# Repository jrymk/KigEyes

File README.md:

# Project KigEyes

Video passthrough and electronic eye for Kigurumi masks

## Project structure

| Directory | Description | Source status |
| --- | --- | --- |
| [companion](companion/) | Android app for connection setup, screen sharing, wearer viewing and phone-camera capture | Published |
| [docs](docs/) | Project documentation and illustrations | Selected files published |
| [drivers](drivers/) | Linux hardware drivers and device services | Partially published |
| `drivers/bluetooth` | Bluetooth compatibility fixes for controller input and haptics | Not published |
| `drivers/ec` | Linux link to the embedded controller: telemetry, commands and shutdown coordination | Not published |
| `drivers/glasses` | AR-glasses display control, IMU readings and orientation processing | Not published |
| [drivers/imx675](drivers/imx675/) | Linux sensor driver and device-tree support for KigEyes IMX675 modules | Core driver published |
| `drivers/imx675/libcamera` | IMX675 camera-stack integration and image-processing tuning | Not published |
| `drivers/imx678` | Experimental driver and bring-up tools for the IMX678 camera module | Not published |
| `firmware` | Microcontroller firmware for the custom boards | Not published |
| `firmware/camera-module` | Camera-module power sequencing, sensor management and synchronization controls | Publishing soon |
| `firmware/mainboard` | Mainboard controller, host communication and board diagnostics | Not published |
| `firmware/power-io-board` | Battery charging, power delivery, protection and power-state control | Not published |
| [integrations](integrations/) | Optional phone-mirroring and media integrations | Phone worker published |
| `integrations/jellyfin` | Jellyfin casting, playback and remote controls | Private |
| [integrations/scrcpy](integrations/scrcpy/) | Pi-side phone receiver, installation tools and Visor integration | Private |
| [integrations/scrcpy/worker](integrations/scrcpy/worker/) | Modified Android scrcpy worker with direct TLS, reconnection and panel controls | Published |
| `integrations/spotify` | Spotify Connect receiver integration and playback controls | Private |
| [licenses](licenses/) | License texts for published software and hardware | Published |
| [PCB](PCB/) | Schematics, PCB layouts and manufacturing files | Selected designs published |
| `PCB/eye-tracker-mainboard` | Eye-tracking controller board development | Publishing soon |
| `PCB/IMX675-camera-module` | Custom IMX675 sensor module and its management circuitry | Publishing soon |
| `PCB/IMX678-renheng-adaptor` | Adapter and management board for the Renheng IMX678 module | Publishing soon |
| `PCB/kigeyes-mainboard` | Compute Module 5 carrier with camera, display and peripheral connections | v1 work in progress |
| [PCB/kigeyes-power-io-board](PCB/kigeyes-power-io-board/) | Battery, charging, power conversion and peripheral power board | v2 work in progress |
| [PCB/OVM6211-bga2lga](PCB/OVM6211-bga2lga/) | OVM6211 sensor package adapter board | Published |
| [PCB/OVM6211-fpc](PCB/OVM6211-fpc/) | Flexible OVM6211 camera board for eye-tracking hardware | Published |
| `STL` | Printable mask parts, mounts and mechanical prototypes | Not published yet |
| `visor` | On-mask passthrough, display composition, HUD and system control | Private |

## Open source status

This project is not fully open source for now.

- **All** general-purpose designs and reusable components that may benefit the open-source community will be released in full, such as camera sensor drivers, breakout boards, and eye tracking algorithms.
- **Most** schematics will be released in full
- **Some** PCB design files and Gerbers remain closed until obsolete
- **Most** firmware and source code will be released in full
- **Some** mechanical design files will be released in full

## KiCad library

KiCad library available at [jrymk/jerrymk_kicad_lib](https://github.com/jrymk/jerrymk_kicad_lib).

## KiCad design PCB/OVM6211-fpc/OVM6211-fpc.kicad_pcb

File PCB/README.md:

# Project KigEyes PCBs

## kigeyes-mainboard

| versions | status |
| :-- | :-- |
| prototype | assembled, waiting for HDMI to DP converter, do not build |
| v1 | pending |

- Type C (custom protocol) power input (up to 15V) from `kigeyes-power-io-board`, includes single USB 2.0, dual USB 3.2 Gen 1, and I2C
- Raspberry Pi Compute Module 5
- HDMI to DisplayPort to Type C DP Alt mode converter
- MIPI camera multiplexer to connect up to 4 cameras (2 active at once)

## kigeyes-power-io-board

|  |  |
| --- | --- |

| versions | status |
| :-- | :-- |
| [v1](https://github.com/jrymk/KigEyes/tree/dbb5fbab16420fb983b5ba6c4678849511922e23/PCB/kigeyes-power-io-board) | finalized, tested |

- USB PD input (up to 15V 3A)
- 1S LiFePO4 BQ25306 charger (up to 3A) and voltage booster
- Type C (custom protocol) power output (5~15V) to `kigeyes-mainboard`
- USB 2.0 hub
- USB Type C DFP (5V 1.5A, USB 3.2 Gen 1, PD-compliant)
- USB Type A DFP (5V 0.9A guaranteed, USB 3.2 Gen 1)
- USB Port AUX (JST PH, USB 2.0)
- USB Port ENV (JST PH, USB 2.0)
- 24V/12V fan output with speed control

## IMX675-camera-module

- IMX675 sensor with
    - reasonable sensor size (1/2.8") for conical M12 lenses for a small opening
    - reasonably high resolution (2592×1944 5.12MP) for clear text reading but not too high to be wasteful by the mediocre resolution of conical lenses, Raspberry Pi processing power, and 1080p AR glasses
    - STARVIS 2 for okay low light performance
- MCU controlled power sequencing, power rail monitoring, and sensor configuration
- LED status indication
- Stereo camera sync signals through the 22P connector

Note: Use opposite-side (B-type) 22P 0.5mm FFC cables

| versions | status |
| :-- | :-- |
| v1 | tested |

## eye-tracker-mainboard

| versions | status |
| :-- | :-- |
| [a1](https://github.com/jrymk/KigEyes/tree/e749d2dd36b2bbe4de054390257230e3775aa7c6/PCB/archive/eye-tracker-mainboard) | scrapped |
| v1 | postponed |

- Dual ESP32P4 processors
- Connectors to `OVM6211-fpc`
- USB 2.0 hub

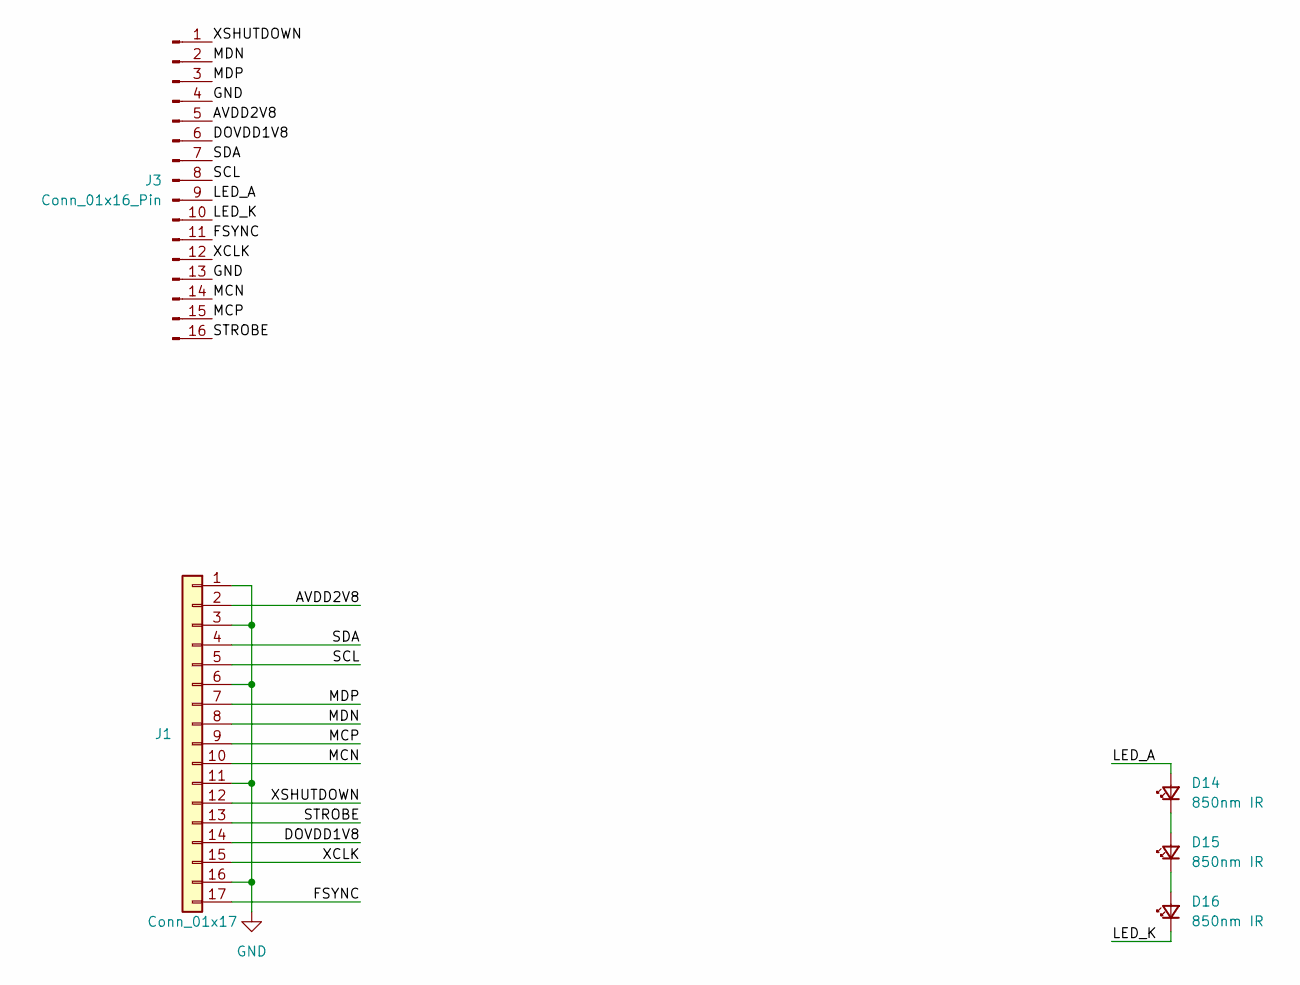
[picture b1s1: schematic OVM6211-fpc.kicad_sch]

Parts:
D14, D15, D16: 850nm IR; LED_0603_1608Metric
J1: Conn_01x17; OVM6211-lga-fp
J3: Conn_01x16_Pin; FFC_16P_BoardEdge

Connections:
/AVDD2V8: J1.2, J3.5
/DOVDD1V8: J1.14, J3.6
/FSYNC: J1.17, J3.11
/LED_A: D14.2 (A), J3.9
/LED_K: D16.1 (K), J3.10
/MCN: J1.10, J3.14
/MCP: J1.9, J3.15
/MDN: J1.8, J3.2
/MDP: J1.7, J3.3
/SCL: J1.5, J3.8
/SDA: J1.4, J3.7
/STROBE: J1.13, J3.16
/XCLK: J1.15, J3.12
/XSHUTDOWN: J1.12, J3.1
GND: J1.1, J1.3, J1.6, J1.11, J1.16, J3.4, J3.13
unnamed: D14.1 (K), D15.2 (A)
unnamed: D15.1 (K), D16.2 (A)

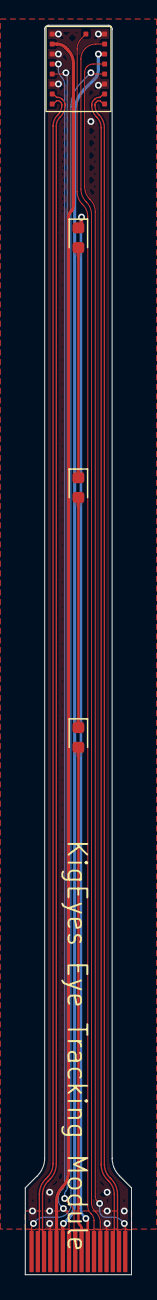
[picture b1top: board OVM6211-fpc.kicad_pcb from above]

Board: 2 copper layers, 8.5 x 100.0 mm, 5 parts (0 on the bottom side), 17 nets.

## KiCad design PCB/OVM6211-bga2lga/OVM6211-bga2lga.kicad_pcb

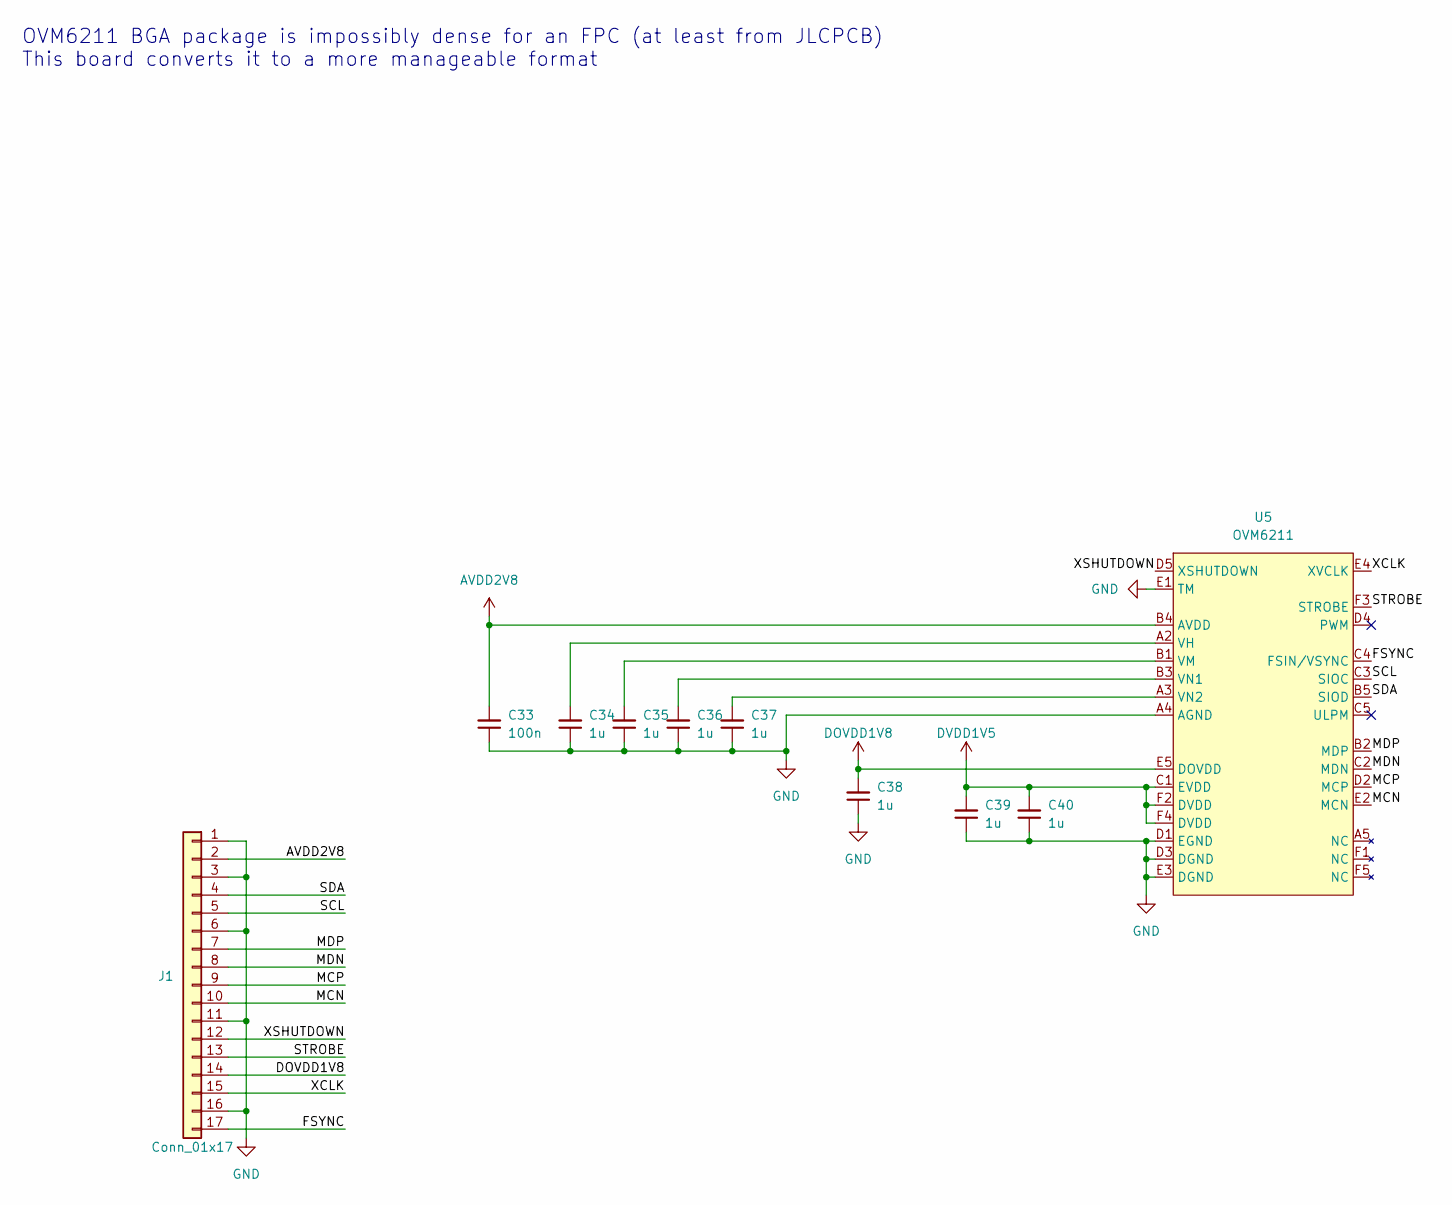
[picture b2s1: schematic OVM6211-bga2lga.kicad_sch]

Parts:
C33: 100n; C_0201_0603Metric
C34, C35, C36, C37, C38, C39, C40: 1u; C_0201_0603Metric
J1: Conn_01x17; OVM6211-lga
U5: OVM6211

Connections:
/FSYNC: J1.17, U5.C4 (FSIN/VSYNC)
/MCN: J1.10, U5.E2 (MCN)
/MCP: J1.9, U5.D2 (MCP)
/MDN: J1.8, U5.C2 (MDN)
/MDP: J1.7, U5.B2 (MDP)
/SCL: J1.5, U5.C3 (SIOC)
/SDA: J1.4, U5.B5 (SIOD)
/STROBE: J1.13, U5.F3 (STROBE)
/XCLK: J1.15, U5.E4 (XVCLK)
/XSHUTDOWN: J1.12, U5.D5 (XSHUTDOWN)
AVDD2V8: C33.2, J1.2, U5.B4 (AVDD)
DOVDD1V8: C38.2, J1.14, U5.E5 (DOVDD)
DVDD1V5: C39.2, C40.2, U5.C1 (EVDD), U5.F2 (DVDD), U5.F4 (DVDD)
GND: C33.1, C34.1, C35.1, C36.1, C37.1, C38.1, C39.1, C40.1, J1.1, J1.3, J1.6, J1.11, J1.16, U5.A4 (AGND), U5.D1 (EGND), U5.D3 (DGND), U5.E1 (TM), U5.E3 (DGND)
unnamed: C34.2, U5.A2 (VH)
unnamed: C35.2, U5.B1 (VM)
unnamed: C36.2, U5.B3 (VN1)
unnamed: C37.2, U5.A3 (VN2)

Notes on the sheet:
OVM6211 BGA package is impossibly dense for an FPC (at least from JLCPCB) This board converts it to a more manageable format

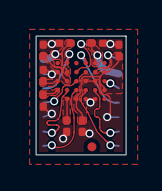
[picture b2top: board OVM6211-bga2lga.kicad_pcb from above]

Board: 4 copper layers, 5.0 x 6.6 mm, 10 parts (0 on the bottom side), 18 nets.

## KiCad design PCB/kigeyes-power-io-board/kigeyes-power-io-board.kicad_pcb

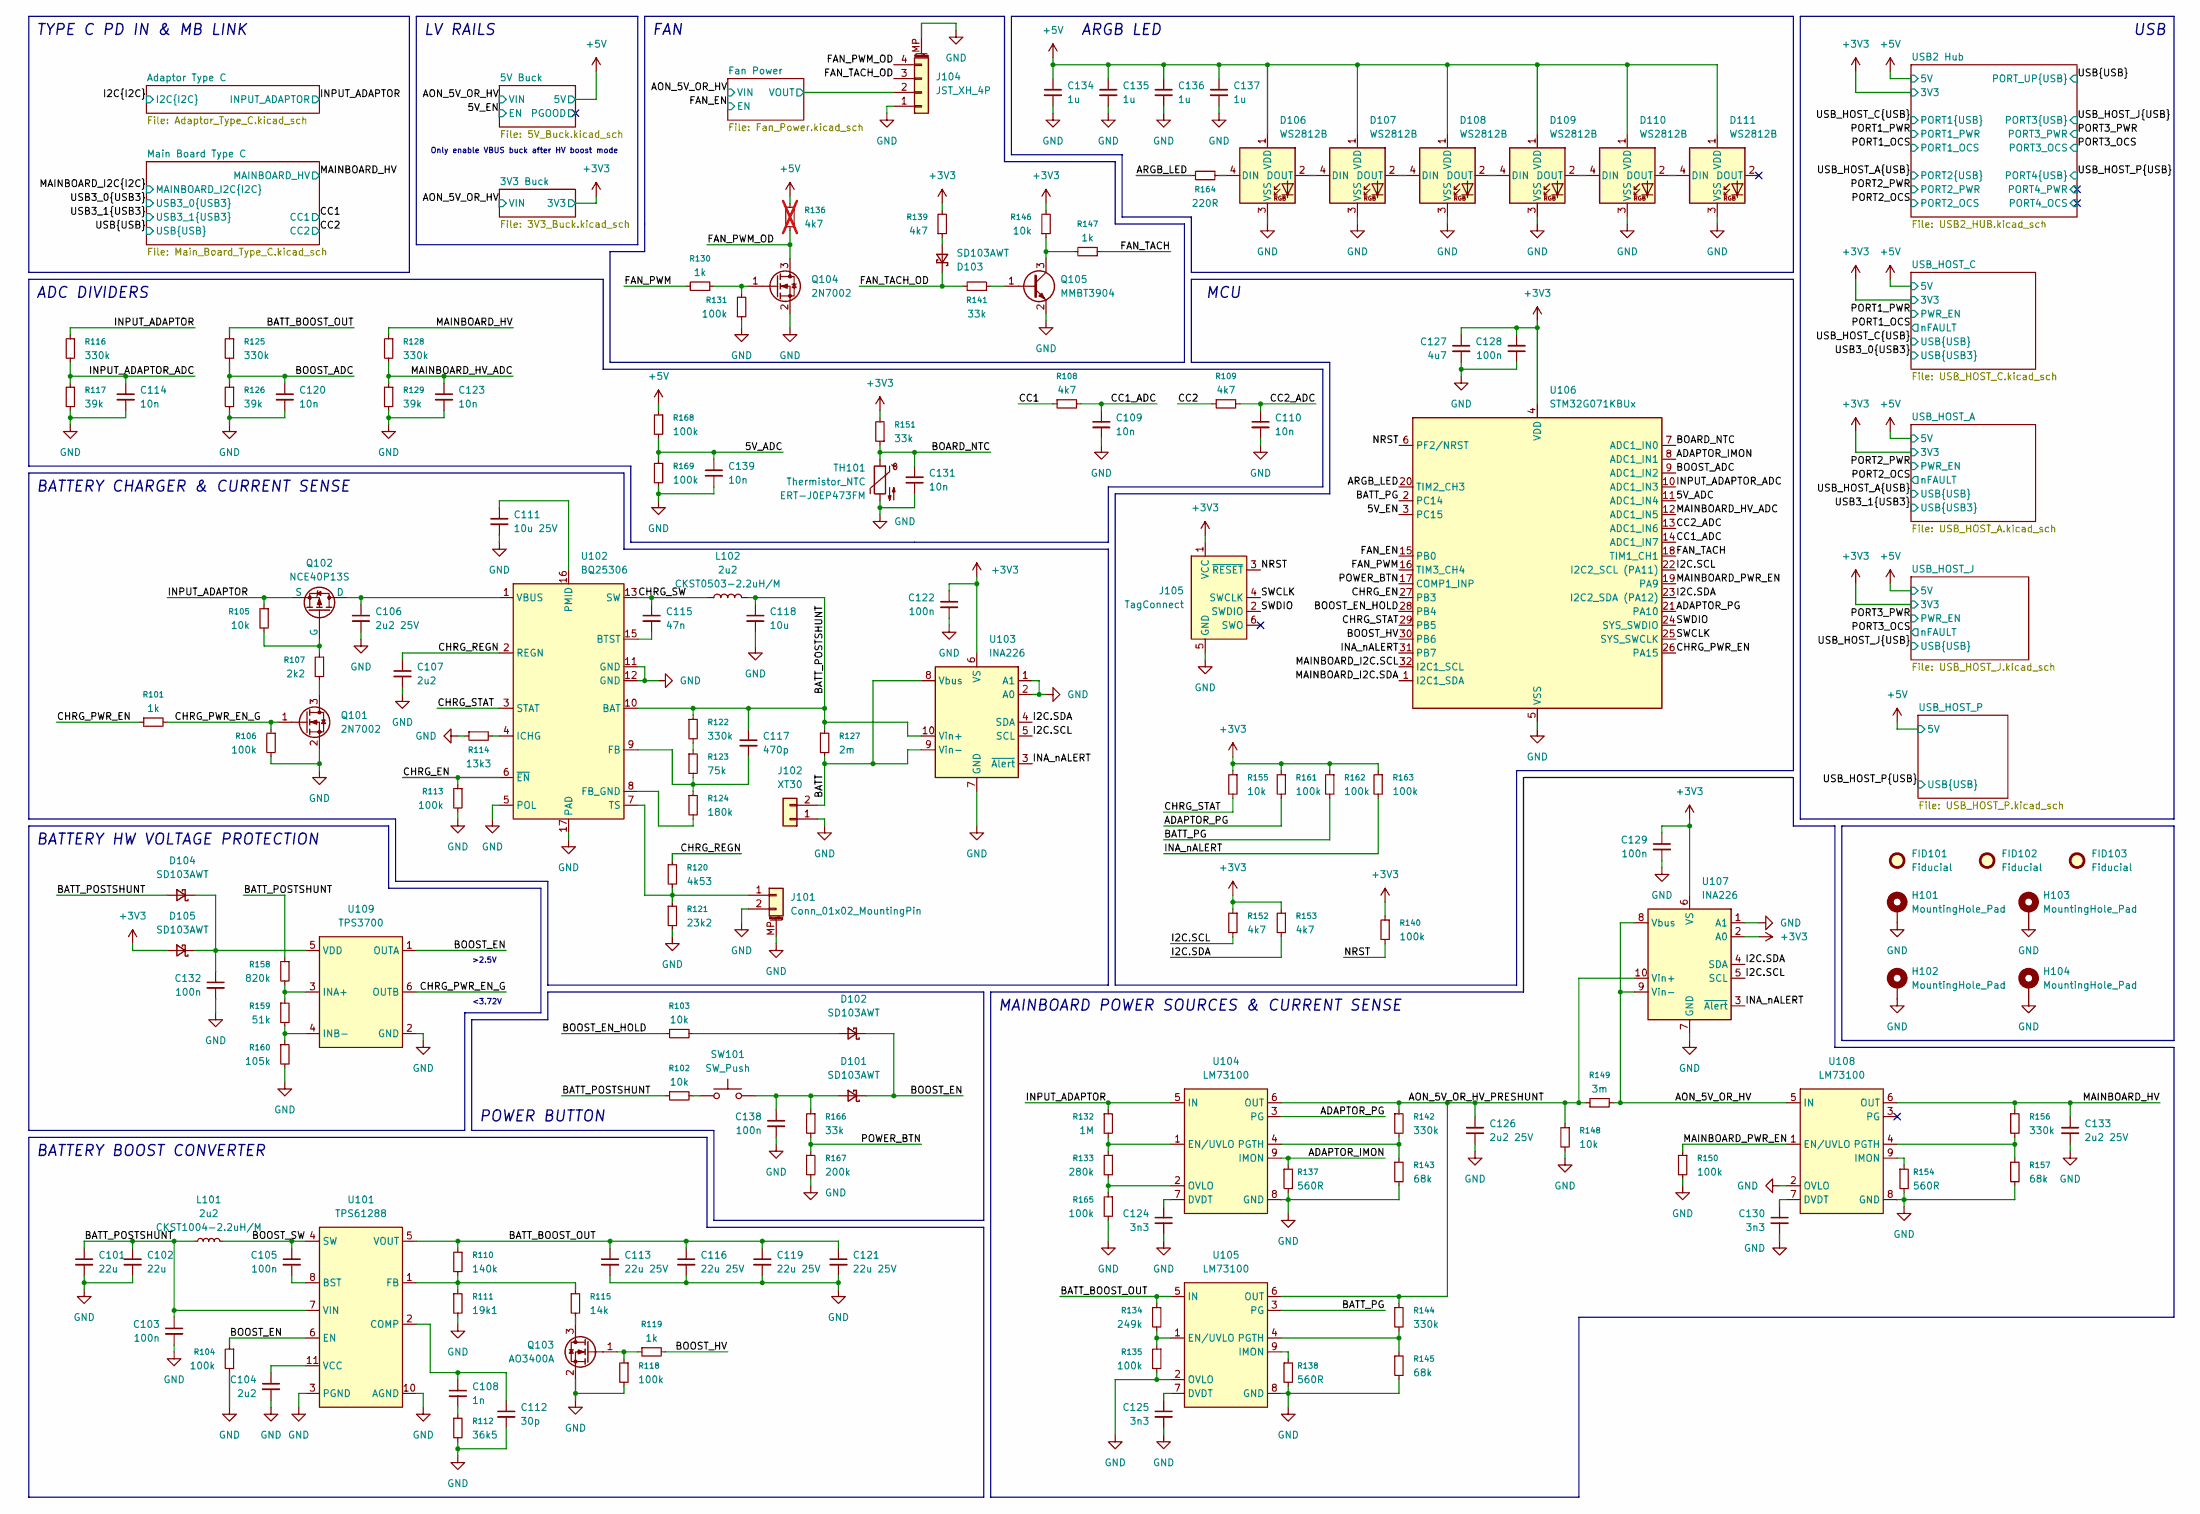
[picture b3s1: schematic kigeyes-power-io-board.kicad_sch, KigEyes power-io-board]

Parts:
C101, C102: 22u; C_0603_1608Metric
C103, C105, C122, C128, C129, C132, C138: 100n; C_0402_1005Metric
C104, C107: 2u2; C_0402_1005Metric
C106, C126, C133: 2u2 25V; C_0603_1608Metric
C108: 1n; C_0402_1005Metric
C109, C110, C114, C120, C123, C131, C139: 10n; C_0402_1005Metric
C111: 10u 25V; C_0805_2012Metric
C112: 30p; C_0402_1005Metric
C113, C116, C119, C121: 22u 25V; C_0805_2012Metric
C115: 47n; C_0402_1005Metric
C117: 470p; C_0402_1005Metric
C118: 10u; C_0603_1608Metric
C124, C125, C130: 3n3; C_0402_1005Metric
C127: 4u7; C_0603_1608Metric
C134, C135, C136, C137: 1u; C_0402_1005Metric
D101, D102, D103, D104, D105: SD103AWT; D_SOD-523
D106, D107, D108, D109, D110, D111: WS2812B; WS2812B-1515
FID101, FID102, FID103: Fiducial; Fiducial_0.5mm_Mask1mm
H101, H102, H103, H104: MountingHole_Pad; MountingHole_2.7mm_M2.5_ISO14580_Pad_TopBottom
J101: Conn_01x02_MountingPin; JST_PH_S2B-PH-SM4-TB_1x02-1MP_P2.00mm_Horizontal
J102: XT30; AMASS_XT30PW-M_1x02_P2.50mm_Horizontal
J104: JST_XH_4P; JST_XH_S4B-XH-SM4-TB_1x04-1MP_P2.50mm_Horizontal
J105: TagConnect; Tag-Connect_TC2030-IDC-NL_2x03_P1.27mm_Vertical
L101: 2u2; L_CKST1004; Part No. CKST1004-2.2uH/M
L102: 2u2; L_CKST0503; Part No. CKST0503-2.2uH/M
Q101, Q104: 2N7002; SOT-23
Q102: NCE40P13S; SOP-8_3.76x4.96mm_P1.27mm_NCE40P13S
Q103: AO3400A; SOT-23
Q105: MMBT3904; SOT-23
R101, R119, R130, R147: 1k; R_0402_1005Metric
R102, R103, R105, R146, R155: 10k; R_0402_1005Metric
R104, R106, R113, R118, R131, R135, R140, R150, R161, R162, R163, R165, R168, R169: 100k; R_0402_1005Metric
R107: 2k2; R_0402_1005Metric
R108, R109, R139, R152, R153: 4k7; R_0402_1005Metric
R110: 140k; R_0402_1005Metric
R111: 19k1; R_0402_1005Metric
R112: 36k5; R_0402_1005Metric
R114: 13k3; R_0402_1005Metric
R115: 14k; R_0402_1005Metric
R116, R122, R125, R128, R142, R144, R156: 330k; R_0402_1005Metric
R117, R126, R129: 39k; R_0402_1005Metric
R120: 4k53; R_0402_1005Metric
R121: 23k2; R_0402_1005Metric
R123: 75k; R_0402_1005Metric
R124: 180k; R_0402_1005Metric
R127: 2m; R_2512_6332Metric
R132: 1M; R_0402_1005Metric
R133: 280k; R_0402_1005Metric
R134: 249k; R_0402_1005Metric
R136: 4k7; R_0402_1005Metric; not fitted
R137, R138, R154: 560R; R_0402_1005Metric
R141, R151, R166: 33k; R_0402_1005Metric
R143, R145, R157: 68k; R_0402_1005Metric
R148: 10k; R_0805_2012Metric
R149: 3m; R_1206_3216Metric
R158: 820k; R_0402_1005Metric
R159: 51k; R_0402_1005Metric
R160: 105k; R_0402_1005Metric
R164: 220R; R_0402_1005Metric
R167: 200k; R_0402_1005Metric
SW101: SW_Push; SW_Tactile_SPST_Angled_PTS645Vx58-2LFS
TH101: Thermistor_NTC; R_0402_1005Metric; Part number ERT-J0EP473FM
U101: TPS61288; Texas_VQFN-HR-20_3x2.5mm_P0.5mm_RQQ0011A
U102: BQ25306; WQFN-16-1EP_3x3mm_P0.5mm_EP1.68x1.68mm
U103, U107: INA226; TSSOP-10_3x3mm_P0.5mm
U104, U105, U108: LM73100; Texas VQFN-HR 2x2mm RPW0010A
U106: STM32G071KBUx; QFN-32-1EP_5x5mm_P0.5mm_EP3.45x3.45mm
U109: TPS3700; SOT-23-6

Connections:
+3V3: C122.1, C127.1, C128.2, C129.1, D105.2 (A), J105.1 (VCC), R139.2, R140.1, R146.2, R151.2, R152.1, R153.1, R155.1, R161.1, R162.1, R163.1, U103.6 (VS), U106.4 (VDD), U107.2 (A0), U107.6 (VS); also elsewhere on the board
+5V: C134.1, C135.1, C136.1, C137.1, D106.1 (VDD), D107.1 (VDD), D108.1 (VDD), D109.1 (VDD), D110.1 (VDD), D111.1 (VDD), R136.1, R168.1; also elsewhere on the board
/5V_ADC: C139.1, R168.2, R169.1, U106.11 (ADC1_IN4)
/5V_EN: U106.3 (PC15); also elsewhere on the board
/ADAPTOR_IMON: R137.1, U104.9 (IMON), U106.8 (ADC1_IN1)
/ADAPTOR_PG: R161.2, U104.3 (PG), U106.21 (PA10)
/AON_5V_OR_HV: R149.2, U107.8 (Vbus), U107.9 (Vin-), U108.5 (IN); also elsewhere on the board
/AON_5V_OR_HV_PRESHUNT: C126.1, R142.1, R144.1, R148.1, R149.1, U104.6 (OUT), U105.6 (OUT), U107.10 (Vin+)
/ARGB_LED: R164.2, U106.20 (TIM2_CH3)
/BATT: J102.2, R127.2, U103.8 (Vbus), U103.9 (Vin-)
/BATT_BOOST_OUT: C113.1, C116.1, C119.1, C121.1, R110.1, R125.1, R134.1, U101.5 (VOUT), U105.5 (IN)
/BATT_PG: R162.2, U105.3 (PG), U106.2 (PC14)
/BATT_POSTSHUNT: C101.1, C102.1, C103.1, C117.1, C118.1, D104.2 (A), L101.1, L102.2, R102.1, R122.1, R127.1, R158.1, U101.7 (VIN), U102.10 (BAT), U103.10 (Vin+)
/BOARD_NTC: C131.2, R151.1, TH101.1, U106.7 (ADC1_IN0)
/BOOST_ADC: C120.1, R125.2, R126.1, U106.9 (ADC1_IN2)
/BOOST_EN: D101.1 (K), D102.1 (K), R104.1, U101.6 (EN), U109.1 (OUTA)
/BOOST_EN_HOLD: R103.1, U106.28 (PB4)
/BOOST_HV: R119.2, U106.30 (PB6)
/BOOST_SW: C105.1, L101.2, U101.4 (SW), U101.9 (SW)
/CC1: R108.1; also elsewhere on the board
/CC1_ADC: C109.1, R108.2, U106.14 (ADC1_IN7)
/CC2: R109.1; also elsewhere on the board
/CC2_ADC: C110.1, R109.2, U106.13 (ADC1_IN6)
/CHRG_EN: R113.1, U102.6 (~EN), U106.27 (PB3)
/CHRG_PWR_EN: R101.1, U106.26 (PA15)
/CHRG_PWR_EN_G: Q101.1 (G), R101.2, R106.1, U109.6 (OUTB)
/CHRG_REGN: C107.1, R120.1, U102.2 (REGN)
/CHRG_STAT: R155.2, U102.3 (STAT), U106.29 (PB5)
/CHRG_SW: C115.1, L102.1, U102.13 (SW), U102.14 (SW)
/FAN_EN: U106.15 (PB0); also elsewhere on the board
/FAN_PWM: R130.2, U106.16 (TIM3_CH4)
/FAN_PWM_OD: J104.4, Q104.3 (D), R136.2
/FAN_TACH: R147.1, U106.18 (TIM1_CH1)
/FAN_TACH_OD: D103.1 (K), J104.3, R141.2
/Fan Power/VOUT: J104.2; also elsewhere on the board
/I2C.SCL: R152.2, U103.5 (SCL), U106.22 (I2C2_SCL (PA11)), U107.5 (SCL); also elsewhere on the board
/I2C.SDA: R153.2, U103.4 (SDA), U106.23 (I2C2_SDA (PA12)), U107.4 (SDA); also elsewhere on the board
/INA_nALERT: R163.2, U103.3 (~Alert), U106.31 (PB7), U107.3 (~Alert)
/INPUT_ADAPTOR: Q102.3 (S), R105.1, R116.1, R132.1, U104.5 (IN); also elsewhere on the board
/INPUT_ADAPTOR_ADC: C114.1, R116.2, R117.1, U106.10 (ADC1_IN3)
/MAINBOARD_HV: C133.1, R128.1, R156.1, U108.6 (OUT); also elsewhere on the board
/MAINBOARD_HV_ADC: C123.1, R128.2, R129.1, U106.12 (ADC1_IN5)
/MAINBOARD_I2C.SCL: U106.32 (I2C1_SCL); also elsewhere on the board
/MAINBOARD_I2C.SDA: U106.1 (I2C1_SDA); also elsewhere on the board
/MAINBOARD_PWR_EN: R150.1, U106.19 (PA9), U108.1 (EN/UVLO)
/NRST: J105.3 (~RESET), R140.2, U106.6 (PF2/NRST)
/POWER_BTN: R166.2, R167.1, U106.17 (COMP1_INP)
/SWCLK: J105.4 (SWCLK), U106.25 (SYS_SWCLK)
/SWDIO: J105.2 (SWDIO), U106.24 (SYS_SWDIO)
GND: C101.2, C102.2, C103.2, C104.2, C106.2, C107.2, C109.2, C110.2, C111.2, C112.2, C113.2, C114.2, C116.2, C118.2, C119.2, C120.2, C121.2, C122.2, C123.2, C124.2, C125.2, C126.2, C127.2, C128.1, C129.2, C130.2, C131.1, C132.2, C133.2, C134.2, C135.2, C136.2, C137.2, C138.2, C139.2, D106.3 (VSS), D107.3 (VSS), D108.3 (VSS), D109.3 (VSS), D110.3 (VSS), D111.3 (VSS), H101.1 (1_1), H102.1 (1_1), H103.1 (1_1), H104.1 (1_1), J101.2, J101.MP (MountPin), J102.1, J104.1, J104.MP (MountPin), J105.5 (GND), Q101.2 (S), Q103.2 (S), Q104.2 (S), Q105.2 (E), R104.2, R106.2, R111.2, R112.2, R113.2, R114.1, R117.2, R118.2, R121.2, R126.2, R129.2, R131.1, R135.2, R137.2, R138.2, R143.2, R145.2, R148.2, R150.2, R154.2, R157.2, R160.2, R165.2, R167.2, R169.2, TH101.2, U101.3 (PGND), U101.10 (AGND), U102.5 (POL), U102.11 (GND), U102.12 (GND), U102.17 (PAD), U103.1 (A1), U103.2 (A0), U103.7 (GND), U104.8 (GND), U105.2 (OVLO), U105.8 (GND), U106.5 (VSS), U106.33 (VSS), U107.1 (A1), U107.7 (GND), U108.2 (OVLO), U108.8 (GND), U109.2 (GND); also elsewhere on the board
unnamed: C108.2, R112.1
unnamed: C138.1, D101.2 (A), R166.1, SW101.1
unnamed: D102.2 (A), R103.2
unnamed: D103.2 (A), R139.1
unnamed: C132.1, D104.1 (K), D105.1 (K), U109.5 (VDD)
unnamed: D106.4 (DIN), R164.1
unnamed: D106.2 (DOUT), D107.4 (DIN)
unnamed: D107.2 (DOUT), D108.4 (DIN)
unnamed: D108.2 (DOUT), D109.4 (DIN)
unnamed: D109.2 (DOUT), D110.4 (DIN)
unnamed: D110.2 (DOUT), D111.4 (DIN)
unnamed: J101.1, R120.2, R121.1, U102.7 (TS)
unnamed: Q101.3 (D), R107.2
unnamed: C106.1, Q102.1 (D), U102.1 (VBUS)
unnamed: Q102.2 (G), R105.2, R107.1
unnamed: Q103.3 (D), R115.2
unnamed: Q103.1 (G), R118.1, R119.1
unnamed: Q104.1 (G), R130.1, R131.2
unnamed: Q105.1 (B), R141.1
unnamed: Q105.3 (C), R146.1, R147.2
unnamed: R102.2, SW101.2
unnamed: R122.2, R123.1
unnamed: C105.2, U101.8 (BST)
unnamed: C108.1, C112.1, U101.2 (COMP)
unnamed: R110.2, R111.1, R115.1, U101.1 (FB)
unnamed: C104.1, U101.11 (VCC)
unnamed: C115.2, U102.15 (BTST)
unnamed: C117.2, R123.2, R124.1, U102.9 (FB)
unnamed: R124.2, U102.8 (FB_GND)
unnamed: R114.2, U102.4 (ICHG)
unnamed: C111.1, U102.16 (PMID)
unnamed: C124.1, U104.7 (DVDT)
unnamed: R132.2, R133.1, U104.1 (EN/UVLO)
unnamed: R133.2, R165.1, U104.2 (OVLO)
unnamed: R142.2, R143.1, U104.4 (PGTH)
unnamed: C125.1, U105.7 (DVDT)
unnamed: R134.2, R135.1, U105.1 (EN/UVLO)
unnamed: R138.1, U105.9 (IMON)
unnamed: R144.2, R145.1, U105.4 (PGTH)
unnamed: C130.1, U108.7 (DVDT)
unnamed: R154.1, U108.9 (IMON)
unnamed: R156.2, R157.1, U108.4 (PGTH)
unnamed: R158.2, R159.1, U109.3 (INA+)
unnamed: R159.2, R160.1, U109.4 (INB-)

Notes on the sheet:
Only enable VBUS buck after HV boost mode
ADC DIVIDERS
<3.72V
BATTERY BOOST CONVERTER
FAN
USB
TYPE C PD IN & MB LINK
ARGB LED
>2.5V
POWER BUTTON
MCU
MAINBOARD POWER SOURCES & CURRENT SENSE
BATTERY HW VOLTAGE PROTECTION
BATTERY CHARGER & CURRENT SENSE
LV RAILS

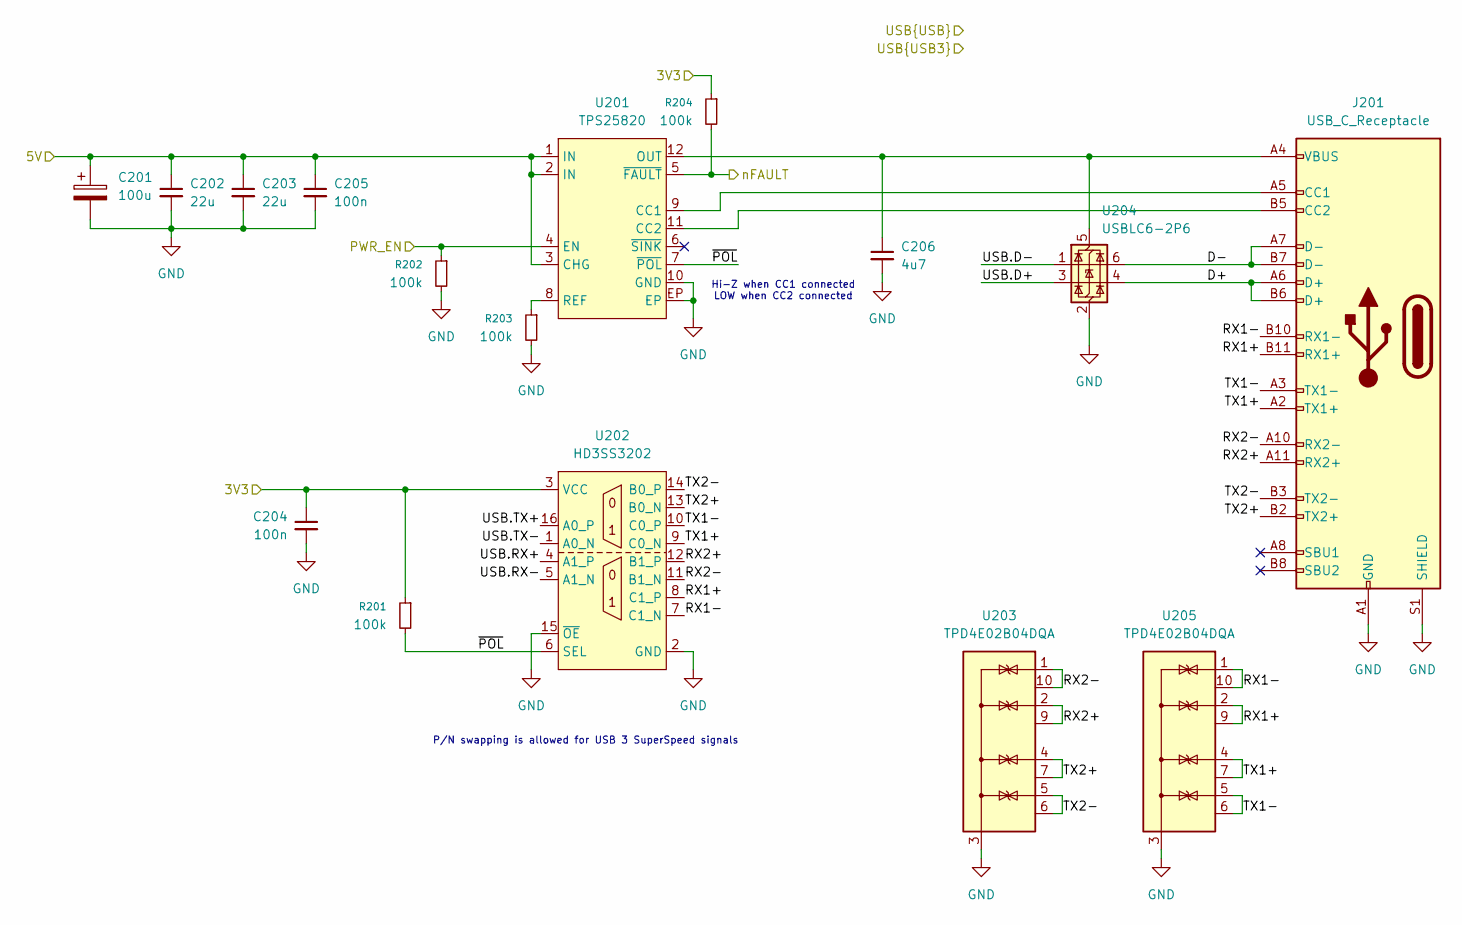
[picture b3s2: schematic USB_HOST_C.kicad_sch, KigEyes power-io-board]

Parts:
C201: 100u; CP_Elec_6.3x5.8
C202, C203: 22u; C_0603_1608Metric
C204, C205: 100n; C_0402_1005Metric
C206: 4u7; C_0603_1608Metric
J201: USB_C_Receptacle; USB_C_Receptacle_GCT_USB4080
R201, R202, R203, R204: 100k; R_0402_1005Metric
U201: TPS25820; Texas WSON-12 P0.5mm 3x2mm EP2.65x1mm DSS0012B
U202: HD3SS3202; Texas UQFN-16_1.8x2.6mm_P0.4mm RSV0016A
U203, U205: TPD4E02B04DQA; Texas USON-10_2.5x1.0mm_P0.5mm DQA0010A
U204: USBLC6-2P6; SOT-666

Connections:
+3V3: C204.1, R201.1, R204.1, U202.3 (VCC); also elsewhere on the board
+5V: C201.1, C202.1, C203.1, C205.1, U201.1 (IN), U201.2 (IN), U201.3 (CHG); also elsewhere on the board
/PORT1_OCS: R204.2, U201.5 (~FAULT); also elsewhere on the board
/PORT1_PWR: R202.1, U201.4 (EN); also elsewhere on the board
/USB3_0.RX+: U202.4 (A1_P); also elsewhere on the board
/USB3_0.RX-: U202.5 (A1_N); also elsewhere on the board
/USB3_0.TX+: U202.16 (A0_P); also elsewhere on the board
/USB3_0.TX-: U202.1 (A0_N); also elsewhere on the board
/USB_HOST_C.D+: U204.3 (I/O2); also elsewhere on the board
/USB_HOST_C.D-: U204.1 (I/O1); also elsewhere on the board
/USB_HOST_C/D+: J201.A6 (D+), J201.B6 (D+), U204.4 (I/O2)
/USB_HOST_C/D-: J201.A7 (D-), J201.B7 (D-), U204.6 (I/O1)
/USB_HOST_C/RX1+: J201.B11 (RX1+), U202.8 (C1_P), U205.2 (IO2), U205.9 (NC)
/USB_HOST_C/RX1-: J201.B10 (RX1-), U202.7 (C1_N), U205.1 (IO1), U205.10 (NC)
/USB_HOST_C/RX2+: J201.A11 (RX2+), U202.12 (B1_P), U203.2 (IO2), U203.9 (NC)
/USB_HOST_C/RX2-: J201.A10 (RX2-), U202.11 (B1_N), U203.1 (IO1), U203.10 (NC)
/USB_HOST_C/TX1+: J201.A2 (TX1+), U202.9 (C0_N), U205.4 (IO3), U205.7 (NC)
/USB_HOST_C/TX1-: J201.A3 (TX1-), U202.10 (C0_P), U205.5 (IO4), U205.6 (NC)
/USB_HOST_C/TX2+: J201.B2 (TX2+), U202.13 (B0_N), U203.4 (IO3), U203.7 (NC)
/USB_HOST_C/TX2-: J201.B3 (TX2-), U202.14 (B0_P), U203.5 (IO4), U203.6 (NC)
/USB_HOST_C/~POL: R201.2, U201.7 (~POL), U202.6 (SEL)
GND: C201.2, C202.2, C203.2, C204.2, C205.2, C206.2, J201.A1 (GND), J201.A12 (GND), J201.B1 (GND), J201.B12 (GND), J201.S1 (SHIELD), R202.2, R203.2, U201.10 (GND), U201.EP, U202.2 (GND), U202.15 (~OE), U203.3 (G), U203.8 (G), U204.2 (GND), U205.3 (G), U205.8 (G); also elsewhere on the board
unnamed: J201.A5 (CC1), U201.9 (CC1)
unnamed: J201.B5 (CC2), U201.11 (CC2)
unnamed: C206.1, J201.A4 (VBUS), J201.A9 (VBUS), J201.B4 (VBUS), J201.B9 (VBUS), U201.12 (OUT), U204.5 (VBUS)
unnamed: R203.1, U201.8 (REF)

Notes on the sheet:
Hi-Z when CC1 connected LOW when CC2 connected
P/N swapping is allowed for USB 3 SuperSpeed signals

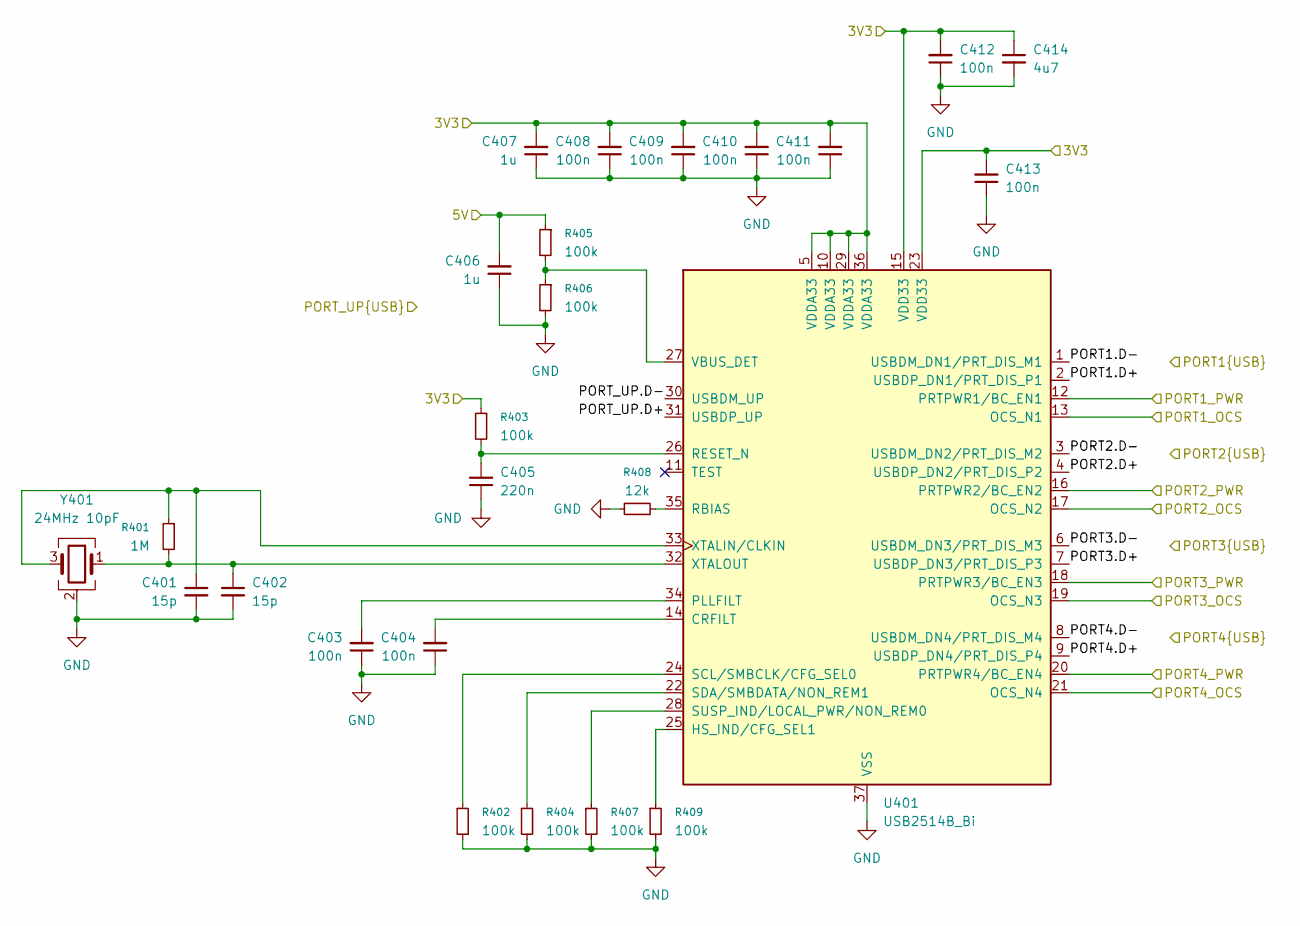
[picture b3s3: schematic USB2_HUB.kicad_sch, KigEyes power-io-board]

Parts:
C401, C402: 15p; C_0402_1005Metric
C403, C404, C408, C409, C410, C411, C412, C413: 100n; C_0402_1005Metric
C405: 220n; C_0402_1005Metric
C406, C407: 1u; C_0402_1005Metric
C414: 4u7; C_0603_1608Metric
R401: 1M; R_0402_1005Metric
R402, R403, R404, R405, R406, R407, R409: 100k; R_0402_1005Metric
R408: 12k; R_0402_1005Metric
U401: USB2514B_Bi; QFN-36-1EP_6x6mm_P0.5mm_EP3.7x3.7mm
Y401: 24MHz 10pF; Crystal_SMD_SeikoEpson_FA238-4Pin_3.2x2.5mm

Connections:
+3V3: C407.2, C408.2, C409.2, C410.2, C411.2, C412.2, C413.2, C414.1, R403.1, U401.5 (VDDA33), U401.10 (VDDA33), U401.15 (VDD33), U401.23 (VDD33), U401.29 (VDDA33), U401.36 (VDDA33); also elsewhere on the board
+5V: C406.2, R405.1; also elsewhere on the board
/PORT1_OCS: U401.13 (OCS_N1); also elsewhere on the board
/PORT1_PWR: U401.12 (PRTPWR1/BC_EN1); also elsewhere on the board
/PORT2_OCS: U401.17 (OCS_N2); also elsewhere on the board
/PORT2_PWR: U401.16 (PRTPWR2/BC_EN2); also elsewhere on the board
/PORT3_OCS: U401.19 (OCS_N3); also elsewhere on the board
/PORT3_PWR: U401.18 (PRTPWR3/BC_EN3); also elsewhere on the board
/USB2 Hub/PORT4_OCS: U401.21 (OCS_N4)
/USB2 Hub/PORT4_PWR: U401.20 (PRTPWR4/BC_EN4)
/USB.D+: U401.31 (USBDP_UP); also elsewhere on the board
/USB.D-: U401.30 (USBDM_UP); also elsewhere on the board
/USB_HOST_A.D+: U401.4 (USBDP_DN2/PRT_DIS_P2); also elsewhere on the board
/USB_HOST_A.D-: U401.3 (USBDM_DN2/PRT_DIS_M2); also elsewhere on the board
/USB_HOST_C.D+: U401.2 (USBDP_DN1/PRT_DIS_P1); also elsewhere on the board
/USB_HOST_C.D-: U401.1 (USBDM_DN1/PRT_DIS_M1); also elsewhere on the board
/USB_HOST_J.D+: U401.7 (USBDP_DN3/PRT_DIS_P3); also elsewhere on the board
/USB_HOST_J.D-: U401.6 (USBDM_DN3/PRT_DIS_M3); also elsewhere on the board
/USB_HOST_P.D+: U401.9 (USBDP_DN4/PRT_DIS_P4); also elsewhere on the board
/USB_HOST_P.D-: U401.8 (USBDM_DN4/PRT_DIS_M4); also elsewhere on the board
GND: C401.2, C402.2, C403.1, C404.1, C405.1, C406.1, C407.1, C408.1, C409.1, C410.1, C411.1, C412.1, C413.1, C414.2, R402.2, R404.2, R406.2, R407.2, R408.1, R409.2, U401.37 (VSS), Y401.2 (G), Y401.4 (G); also elsewhere on the board
unnamed: C404.2, U401.14 (CRFILT)
unnamed: R409.1, U401.25 (HS_IND/CFG_SEL1)
unnamed: C403.2, U401.34 (PLLFILT)
unnamed: R408.2, U401.35 (RBIAS)
unnamed: C405.2, R403.2, U401.26 (RESET_N)
unnamed: R402.1, U401.24 (SCL/SMBCLK/CFG_SEL0)
unnamed: R404.1, U401.22 (SDA/SMBDATA/NON_REM1)
unnamed: R407.1, U401.28 (SUSP_IND/LOCAL_PWR/NON_REM0)
unnamed: R405.2, R406.1, U401.27 (VBUS_DET)
unnamed: C401.1, R401.1, U401.33 (XTALIN/CLKIN), Y401.3
unnamed: C402.1, R401.2, U401.32 (XTALOUT), Y401.1
